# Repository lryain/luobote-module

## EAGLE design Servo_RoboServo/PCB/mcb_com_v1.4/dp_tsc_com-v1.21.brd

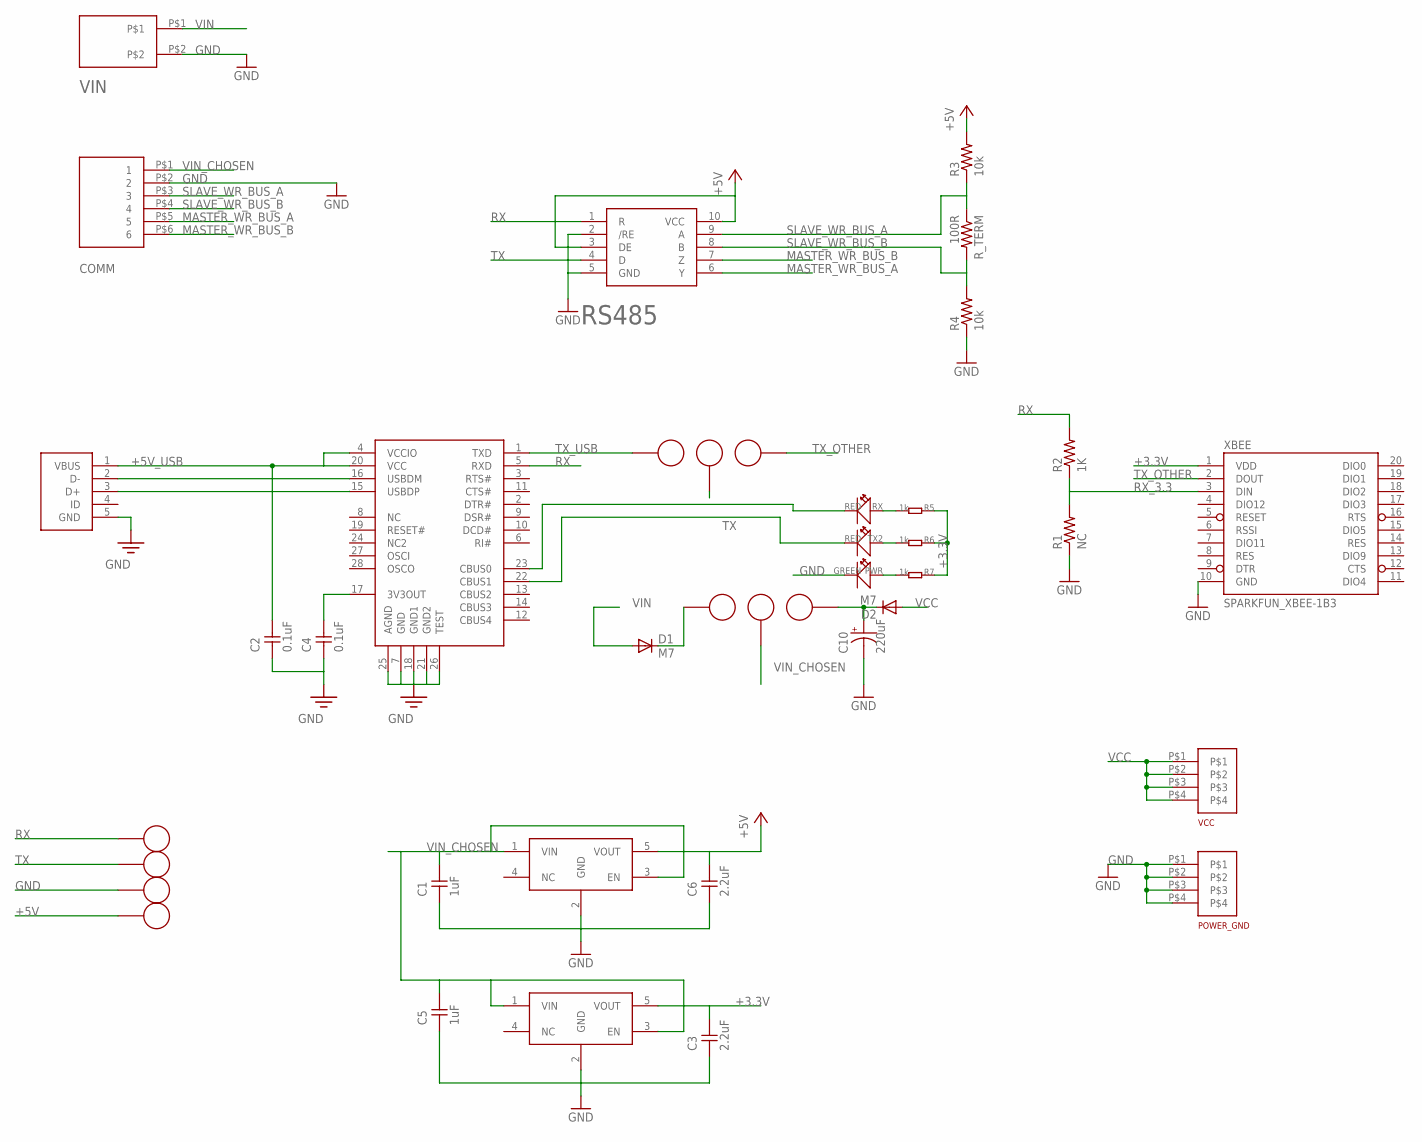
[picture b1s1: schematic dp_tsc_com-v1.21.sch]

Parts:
3.3V_REG, 5V_REG: MIC5235; SOT-23-5
5V1, 5V_USB1, 5V_VREG1: CONNECTOR_TV
+5V: CONNECTOR_TV
C1, C5: 1uF; 0805@1
C2, C4: 0.1uF; 0805@1
C3, C6: 2.2uF; 0805@1
C10: 220uF; HAO
COMM: 6PIN-RIBBONCABLE-BOARDHEADER; 6PIN-HEADER-DUALROW
D1, D2: M7; DO214BA
FT323R: FT232R; SSOP-28
GND: CONNECTOR_TV
POWER_GND: SCREW_TERMINAL_7700K; SCREW_TERM_7700K
PWR: GREEN; LED0603_S
R1: NC; 0603
R2: 1K; 0603
R3, R4: 10k; 0603
R5, R6, R7: 1k; 0603_S
RS485: RS485-SN65HVD3086EDGSR; MSOP-10
RX: RED; LED0603_S
RX1: CONNECTOR_TV
R_TERM: 100R; 0603
TX, TX1: CONNECTOR_TV
TX2: RED; LED0603_S
TX_FTDI: CONNECTOR_TV
TX_TTL: CONNECTOR_TV
USB: MINIUSB; UX60-MINI-USB
VCC: SCREW_TERMINAL_7700K; SCREW_TERM_7700K
VIN: 2PIN-3.81MM-TERMINAL-BLOCK; 2PIN-TERMINAL-BLOCK-SMALLER
XBEE: SPARKFUN_XBEE-1B3; SPARKFUN_XBEE-SMD

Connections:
+3.3V: 3.3V_REG.5 (VOUT), C3.2, R5.1, R6.1, R7.1, XBEE.1 (VDD)
+5V: 5V_REG.5 (VOUT), +5V.P$1, C6.2, R3.2, RS485.3 (DE), RS485.10 (VCC)
+5V_USB: C2.2, FT323R.4 (VCCIO), FT323R.20 (VCC), USB.1 (VBUS)
D+: FT323R.15 (USBDP), USB.3 (D+)
D-: FT323R.16 (USBDM), USB.2 (D-)
GND: 3.3V_REG.2 (GND), 5V_REG.2 (GND), C1.1, C2.1, C3.1, C4.1, C5.1, C6.1, C10.-, COMM.P$2 (2), FT323R.7 (GND), FT323R.18 (GND1), FT323R.21 (GND2), FT323R.25 (AGND), FT323R.26 (TEST), GND.P$1, POWER_GND.P$1, POWER_GND.P$2, POWER_GND.P$3, POWER_GND.P$4, PWR.2 (-), R1.1, R4.1, RS485.2 (/RE), RS485.5 (GND), USB.5 (GND), VIN.P$2, XBEE.10 (GND)
MASTER_WR_BUS_A: COMM.P$5 (5), RS485.6 (Y)
MASTER_WR_BUS_B: COMM.P$6 (6), RS485.7 (Z)
unnamed: 5V_USB1.P$1, C10.+, D2.C
unnamed: R6.2, TX2.1 (+)
unnamed: R5.2, RX.1 (+)
unnamed: C4.2, FT323R.17 (3V3OUT)
unnamed: PWR.1 (+), R7.2
unnamed: 5V_VREG1.P$1, D1.C
RX: FT323R.5 (RXD), R2.2, RS485.1 (R), RX1.P$1
RXING: FT323R.23 (CBUS0), RX.2 (-)
RX_3.3: R1.2, R2.1, XBEE.3 (DIN)
SLAVE_WR_BUS_A: COMM.P$3 (3), R3.1, RS485.9 (A), R_TERM.1
SLAVE_WR_BUS_B: COMM.P$4 (4), R4.2, RS485.8 (B), R_TERM.2
TX: RS485.4 (D), TX.P$1, TX1.P$1
TXING: FT323R.22 (CBUS1), TX2.2 (-)
TX_OTHER: TX_TTL.P$1, XBEE.2 (DOUT)
TX_USB: FT323R.1 (TXD), TX_FTDI.P$1
VCC: D2.A, VCC.P$1, VCC.P$2, VCC.P$3, VCC.P$4
VIN: D1.A, VIN.P$1
VIN_CHOSEN: 3.3V_REG.1 (VIN), 3.3V_REG.3 (EN), 5V1.P$1, 5V_REG.1 (VIN), 5V_REG.3 (EN), C1.2, C5.2, COMM.P$1 (1)

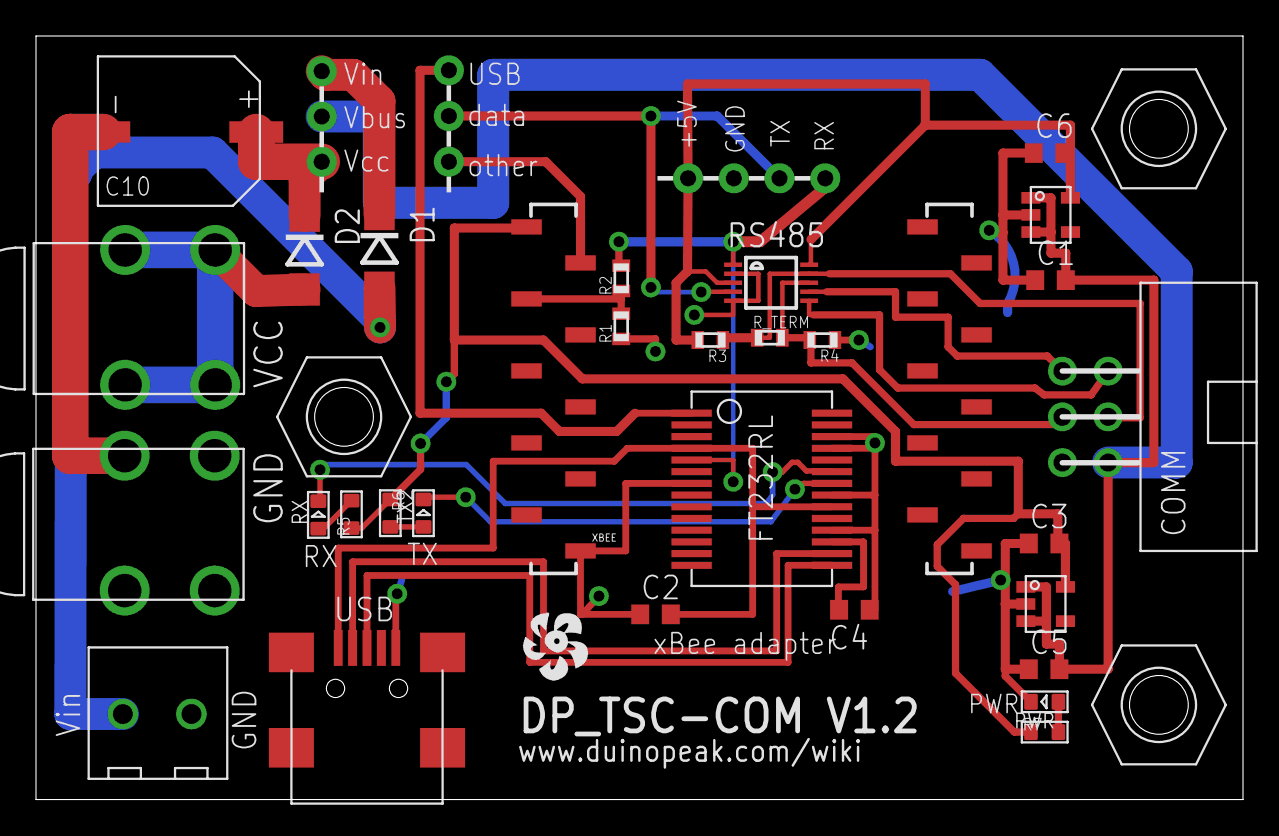
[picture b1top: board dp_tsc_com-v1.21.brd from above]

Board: 2 copper layers, 67.1 x 42.4 mm, 45 parts (0 on the bottom side), 26 nets.

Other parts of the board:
U$1: DUINOFUN-LOGO-PCB-0.5
U$2, U$3, U$14: 4-40_NUT_DRILL
U$5: DUINOFUN-BIG-LOGO-3.0

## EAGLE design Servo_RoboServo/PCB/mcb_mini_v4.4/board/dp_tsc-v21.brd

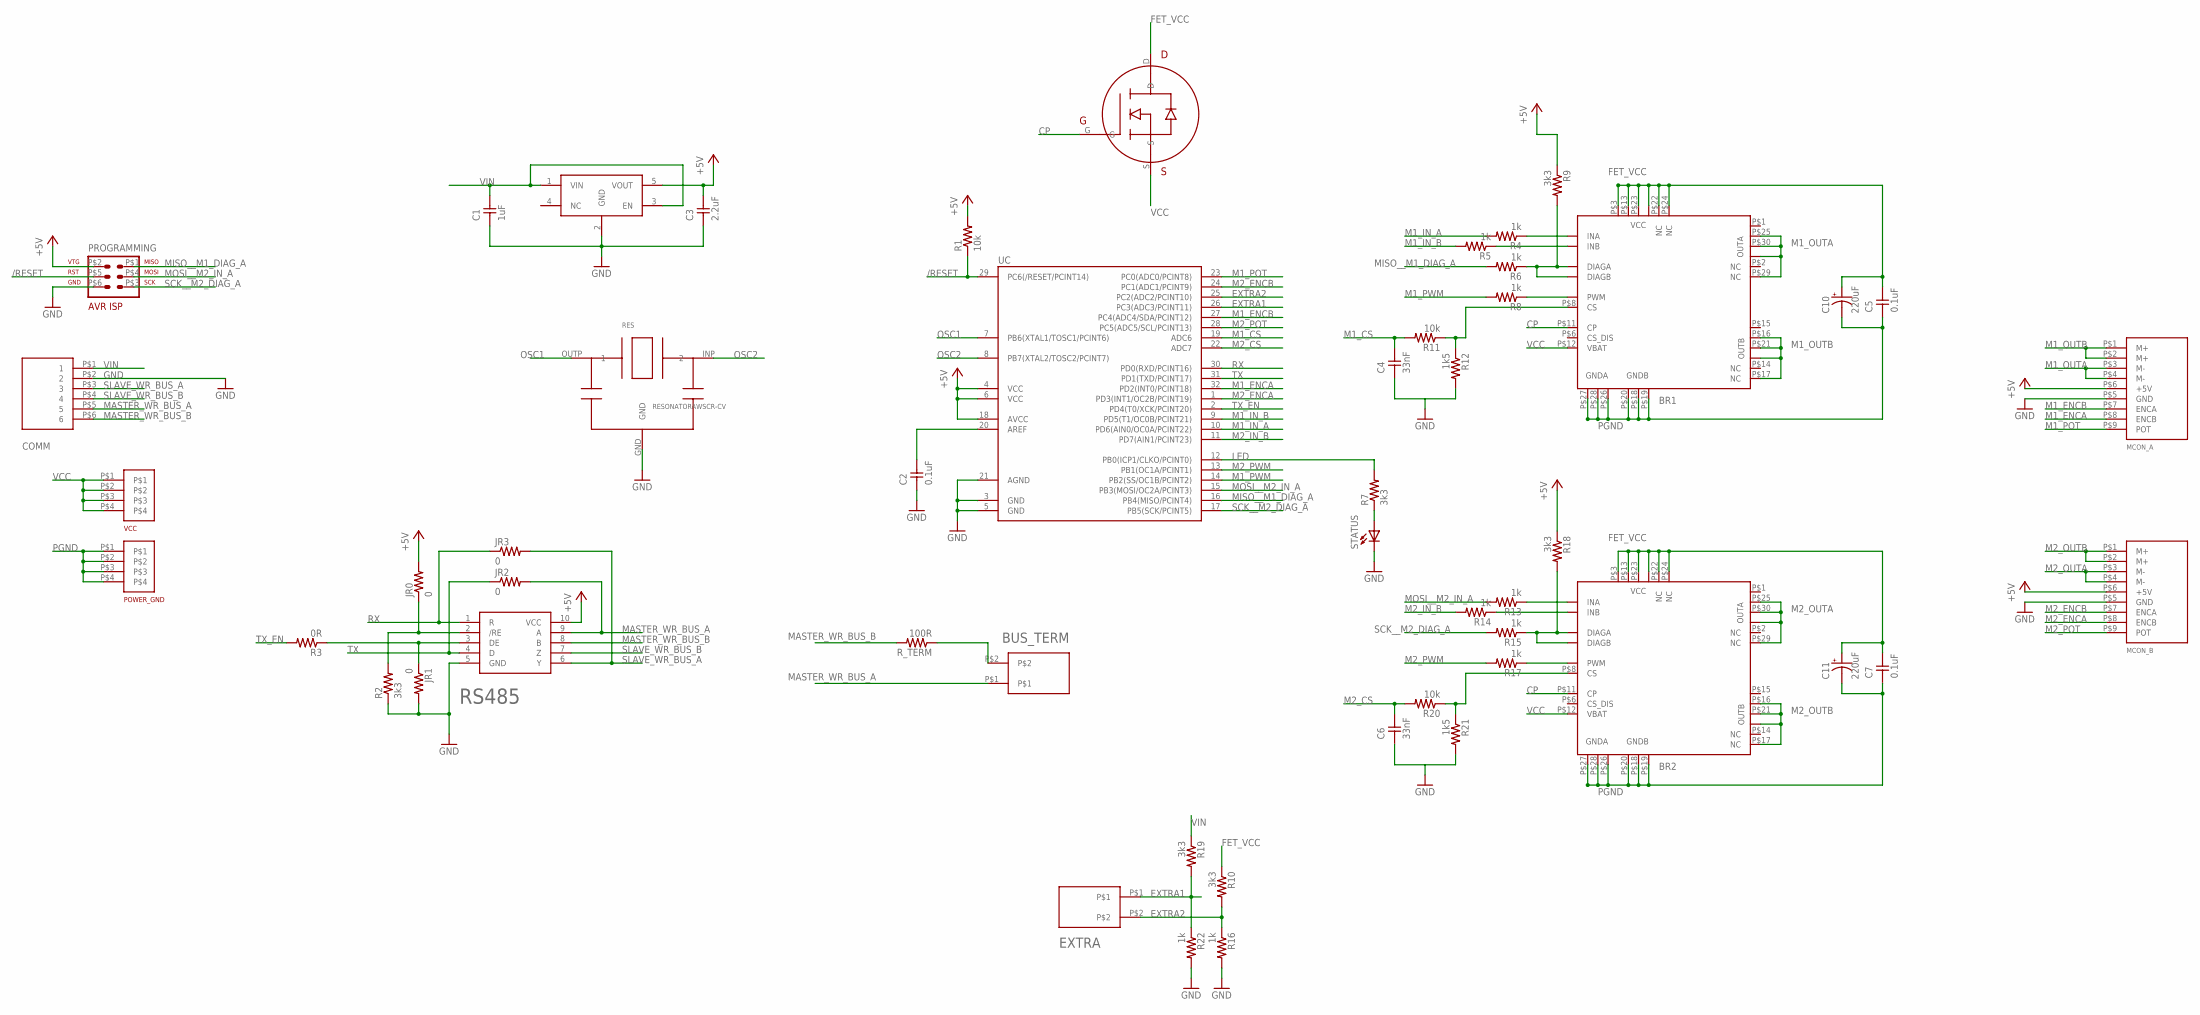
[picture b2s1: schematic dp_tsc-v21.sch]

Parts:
BR1, BR2: VNH5019A-E; MULTIPOWERSO-30-SIGGI
BUS_TERM: 2PIN-100MILL; 2-PIN-100MIL
C1: 1uF; 0603
C2, C5, C7: 0.1uF; 0603
C3: 2.2uF; 0603
C4, C6: 33nF; 0603
C10, C11: 220uF; HAO
COMM: 6PIN-RIBBONCABLE-BOARDHEADER; 6PIN-HEADER-DUALROW
EXTRA: 2PIN-100MILL; 2-PIN-100MIL
FET: MOSFET-N-FDD8896; TO-252
JR0, JR1, JR2, JR3: 0; 0603
MCON_A: 9-PIN-MOTOR_CONNECTOR; 9-PIN-2.54MM-TERMINAL-BLOCK
MCON_B: 9-PIN-MOTOR_CONNECTOR; 9-PIN-2.54MM-TERMINAL-BLOCK
POWER_GND: SCREW_TERMINAL_7700K; SCREW_TERM_7700K
PROGRAMMING: AVR-ISP-6SURFACE_MOUNT; SMD6
R1, R11, R20: 10k; 0603
R2, R7, R9, R10, R18, R19: 3k3; 0603
R3: 0R; 0603
R4, R5, R6, R8, R13, R14, R15, R16, R17, R22: 1k; 0603
R12, R21: 1k5; 0603
RES: RESONATORAWSCR-CV; AWSCR-CV
RS485: RS485-SN65HVD3086EDGSR; MSOP-10
R_TERM: 100R; 0603
STATUS: LED1206; CHIPLED_1206
UC: MEGA48/88/168-AU; TQFP32-08
VCC: SCREW_TERMINAL_7700K; SCREW_TERM_7700K
VREG: MIC5235; SOT-23-5

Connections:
+1.1V: C2.2, UC.20 (AREF)
+5V: C3.2, JR0.2, MCON_A.P$6 (+5V), MCON_B.P$6 (+5V), PROGRAMMING.P$2 (2), R1.2, R9.1, R18.1, RS485.10 (VCC), UC.4 (VCC), UC.6 (VCC), UC.18 (AVCC), VREG.5 (VOUT)
/RESET: PROGRAMMING.P$5 (5), R1.1, UC.29 (PC6(/RESET/PCINT14))
CP: BR1.P$11 (CP), BR2.P$11 (CP), FET.G
EXTRA1: EXTRA.P$1, R19.2, R22.1, UC.26 (PC3(ADC3/PCINT11))
EXTRA2: EXTRA.P$2, R10.2, R16.1, UC.25 (PC2(ADC2/PCINT10))
FET_VCC: BR1.P$3 (VCC), BR1.P$13 (VCC), BR1.P$22 (NC), BR1.P$23 (VCC), BR1.P$24 (NC), BR1.VCC_SLUG (VCC), BR2.P$3 (VCC), BR2.P$13 (VCC), BR2.P$22 (NC), BR2.P$23 (VCC), BR2.P$24 (NC), BR2.VCC_SLUG (VCC), C5.2, C7.2, C10.+, C11.+, FET.D, R10.1
GND: C1.1, C2.1, C3.1, C4.1, C6.1, COMM.P$2 (2), JR1.2, MCON_A.P$5 (GND), MCON_B.P$5 (GND), PROGRAMMING.P$6 (6), R2.1, R12.2, R16.2, R21.2, R22.2, RES.GND, RS485.5 (GND), STATUS.C, UC.3 (GND), UC.5 (GND), UC.21 (AGND), VREG.2 (GND)
LED: R7.2, UC.12 (PB0(ICP1/CLKO/PCINT0))
M1_CS: C4.2, R11.2, UC.19 (ADC6)
M1_ENCA: MCON_A.P$8 (ENCB), UC.32 (PD2(INT0/PCINT18))
M1_ENCB: MCON_A.P$7 (ENCA), UC.27 (PC4(ADC4/SDA/PCINT12))
M1_IN_A: R4.2, UC.10 (PD6(AIN0/OC0A/PCINT22))
M1_IN_B: R5.2, UC.9 (PD5(T1/OC0B/PCINT21))
M1_OUTA: BR1.OUTA_SLUG (OUTA), BR1.P$25 (OUTA), BR1.P$29 (NC), BR1.P$30 (OUTA), MCON_A.P$3 (M-), MCON_A.P$4 (M-)
M1_OUTB: BR1.OUTB_SLUG (OUTB), BR1.P$16 (OUTB), BR1.P$17 (NC), BR1.P$21 (OUTB), MCON_A.P$1 (M+), MCON_A.P$2 (M+)
M1_POT: MCON_A.P$9 (POT), UC.23 (PC0(ADC0/PCINT8))
M1_PWM: R8.2, UC.14 (PB2(SS/OC1B/PCINT2))
M2_CS: C6.2, R20.2, UC.22 (ADC7)
M2_ENCA: MCON_B.P$8 (ENCB), UC.1 (PD3(INT1/OC2B/PCINT19))
M2_ENCB: MCON_B.P$7 (ENCA), UC.24 (PC1(ADC1/PCINT9))
M2_IN_B: R14.2, UC.11 (PD7(AIN1/PCINT23))
M2_OUTA: BR2.OUTA_SLUG (OUTA), BR2.P$25 (OUTA), BR2.P$29 (NC), BR2.P$30 (OUTA), MCON_B.P$3 (M-), MCON_B.P$4 (M-)
M2_OUTB: BR2.OUTB_SLUG (OUTB), BR2.P$16 (OUTB), BR2.P$17 (NC), BR2.P$21 (OUTB), MCON_B.P$1 (M+), MCON_B.P$2 (M+)
M2_POT: MCON_B.P$9 (POT), UC.28 (PC5(ADC5/SCL/PCINT13))
M2_PWM: R17.2, UC.13 (PB1(OC1A/PCINT1))
MASTER_WR_BUS_A: BUS_TERM.P$1, COMM.P$5 (5), JR2.2, RS485.9 (A)
MASTER_WR_BUS_B: COMM.P$6 (6), RS485.8 (B), R_TERM.2
MISO__M1_DIAG_A: PROGRAMMING.P$1 (1), R6.2, UC.16 (PB4(MISO/PCINT4))
MOSI__M2_IN_A: PROGRAMMING.P$4 (4), R13.2, UC.15 (PB3(MOSI/OC2A/PCINT3))
unnamed: BR2.P$4 (INA), R13.1
unnamed: JR0.1, R2.2, RS485.2 (/RE)
unnamed: JR1.1, R3.1, RS485.3 (DE)
unnamed: BR1.P$8 (CS), R11.1, R12.1
unnamed: BR2.P$10 (INB), R14.1
unnamed: BR2.P$5 (DIAGA), BR2.P$9 (DIAGB), R15.1, R18.2
unnamed: BR2.P$7 (PWM), R17.1
unnamed: BR1.P$4 (INA), R4.1
unnamed: BR1.P$10 (INB), R5.1
unnamed: R7.1, STATUS.A
unnamed: BR1.P$5 (DIAGA), BR1.P$9 (DIAGB), R6.1, R9.2
unnamed: BR1.P$7 (PWM), R8.1
unnamed: BR2.P$8 (CS), R20.1, R21.1
unnamed: BUS_TERM.P$2, R_TERM.1
OSC1: RES.OUTP (1), UC.7 (PB6(XTAL1/TOSC1/PCINT6))
OSC2: RES.INP (2), UC.8 (PB7(XTAL2/TOSC2/PCINT7))
PGND: BR1.P$18 (GNDB), BR1.P$19 (GNDB), BR1.P$20 (GNDB), BR1.P$26 (GNDA), BR1.P$27 (GNDA), BR1.P$28 (GNDA), BR2.P$18 (GNDB), BR2.P$19 (GNDB), BR2.P$20 (GNDB), BR2.P$26 (GNDA), BR2.P$27 (GNDA), BR2.P$28 (GNDA), C5.1, C7.1, C10.-, C11.-, POWER_GND.P$1, POWER_GND.P$2, POWER_GND.P$3, POWER_GND.P$4
RX: JR3.1, RS485.1 (R), UC.30 (PD0(RXD/PCINT16))
SCK__M2_DIAG_A: PROGRAMMING.P$3 (3), R15.2, UC.17 (PB5(SCK/PCINT5))
SLAVE_WR_BUS_A: COMM.P$3 (3), JR3.2, RS485.6 (Y)
SLAVE_WR_BUS_B: COMM.P$4 (4), RS485.7 (Z)
TX: JR2.1, RS485.4 (D), UC.31 (PD1(TXD/PCINT17))
TX_EN: R3.2, UC.2 (PD4(T0/XCK/PCINT20))
VCC: BR1.P$12 (VBAT), BR2.P$12 (VBAT), FET.S, VCC.P$1, VCC.P$2, VCC.P$3, VCC.P$4
VIN: C1.2, COMM.P$1 (1), R19.1, VREG.1 (VIN), VREG.3 (EN)

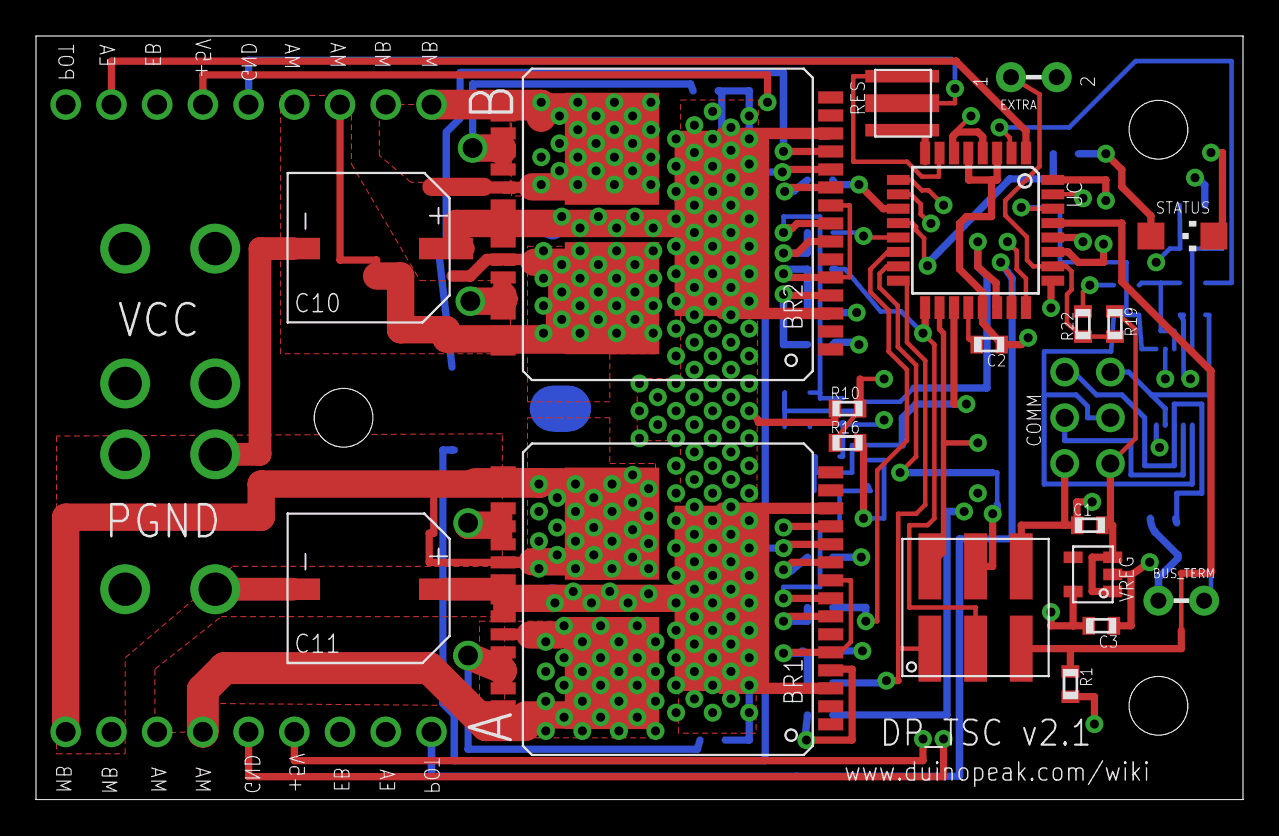
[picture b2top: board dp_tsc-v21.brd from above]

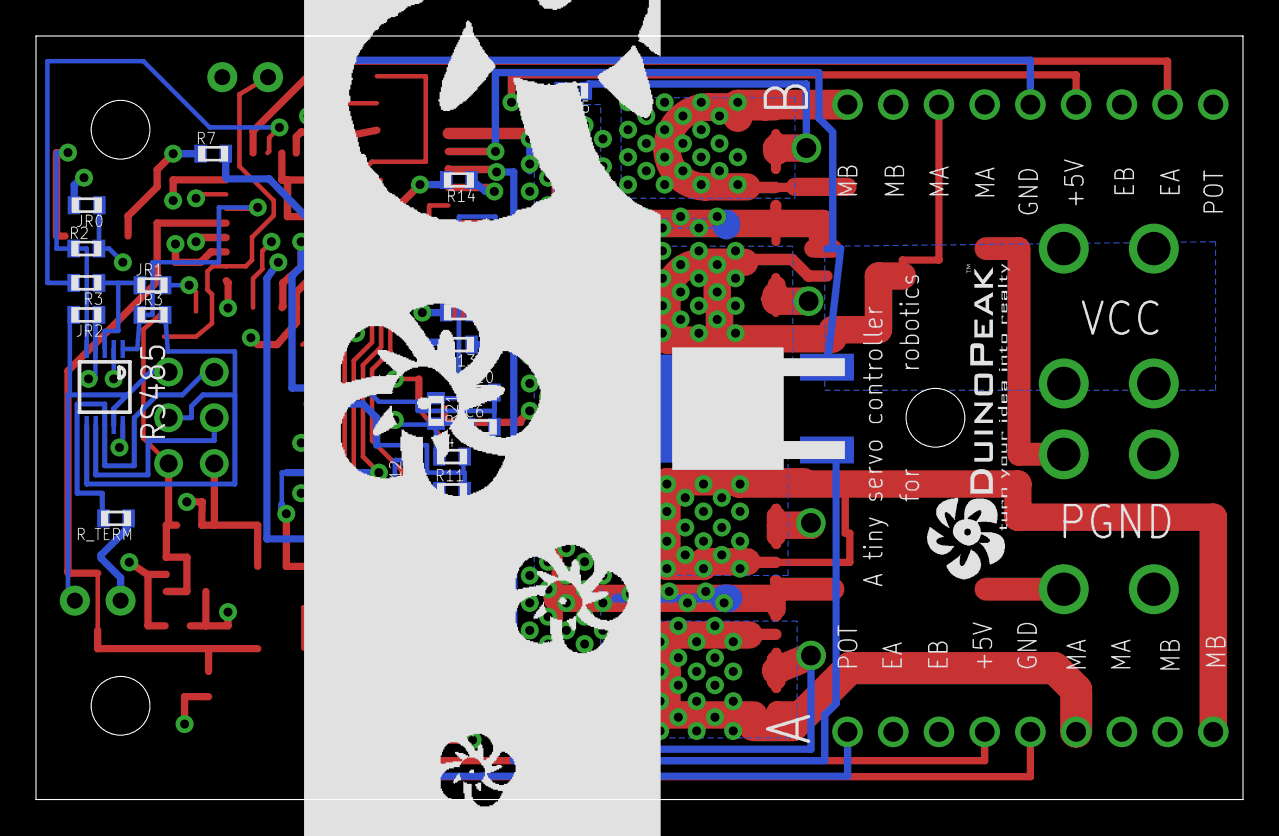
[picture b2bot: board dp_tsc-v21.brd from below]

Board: 2 copper layers, 67.1 x 42.4 mm, 57 parts (29 on the bottom side), 55 nets.

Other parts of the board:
U$1: DUINOFUN-BIG-LOGO-2.6
U$2: DUINOPEAK-LOGO-0.6
U$3, U$10, U$14: 4-40_NUT_DRILL

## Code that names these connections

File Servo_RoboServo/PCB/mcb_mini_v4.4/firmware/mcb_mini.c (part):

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			CLEARBIT(EXTRA1_DDR, EXTRA1);
			SETBIT(EXTRA1_PORT, EXTRA1);
			SETBIT(PCMSK1, EXTRA1);
			motor[channel].extra_switch = BITVAL(EXTRA1_PIN, EXTRA1);
			// Send the current level of the switch
			SETBIT( RX_FLAGS, FLAG_SHOULD_SEND_EXTRA_VAL_A );
		}
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			CLEARBIT(EXTRA2_DDR, EXTRA2);
			SETBIT(EXTRA2_PORT, EXTRA2);
			SETBIT(PCMSK1, EXTRA2);
			motor[channel].extra_switch = BITVAL(EXTRA2_PIN, EXTRA2);
			// Send the current level of the switch
			SETBIT( RX_FLAGS, FLAG_SHOULD_SEND_EXTRA_VAL_B );
		}
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	SETBIT(EIMSK, INT1);

	// Sets the bridge into High z state
	M1_PWM = 0;
	M2_PWM = 0;

	// Init uart
	SETBIT(UCSR0B, RXCIE0);
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// This gets called whenever the EXTRA pins are setup as switches and change value
ISR(PCINT1_vect){
	// If it was EXTRA1
	if( BITVAL(EXTRA1_PIN, EXTRA1) != motor[0].extra_switch ){
		motor[0].extra_switch = BITVAL(EXTRA1_PIN, EXTRA1);
		SETBIT( RX_FLAGS, FLAG_SHOULD_SEND_EXTRA_VAL_A );
	}
	if( BITVAL(EXTRA2_PIN, EXTRA2) != motor[1].extra_switch ){
		motor[1].extra_switch = BITVAL(EXTRA2_PIN, EXTRA2);
		SETBIT( RX_FLAGS, FLAG_SHOULD_SEND_EXTRA_VAL_B );
	}
}
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//		addMessage1(CMD_ERROR, 0, ERROR_FAULT);

		// Reset the bridge
		M1_PWM = 0;
		M1_STOP_GND;
		_delay_us(100);
		M1_STOP_VCC;
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//		addMessage1(CMD_ERROR, 1, ERROR_FAULT);

		// Reset the bridge
		M2_PWM = 0;
		M2_STOP_GND;
		_delay_us(100);
		M2_STOP_VCC;
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
// M1_ENCA changed state
ISR(INT0_vect){
	if( BITSET(M1_ENCB_PIN, M1_ENCB) ){
		if( BITSET(M1_ENCA_PIN, M1_ENCA) ) 	motor[0].encoder_increment--;
		else								motor[0].encoder_increment++;
	}
	else{
		if( BITSET(M1_ENCA_PIN, M1_ENCA) ) 	motor[0].encoder_increment++;
		else								motor[0].encoder_increment--;
	}
}

// M2_ENCA changed state
ISR(INT1_vect){
	if( BITSET(M2_ENCB_PIN, M2_ENCB) ){
		if( BITSET(M2_ENCA_PIN, M2_ENCA) ) 	motor[1].encoder_increment--;
		else								motor[1].encoder_increment++;
	}
	else{
		if( BITSET(M2_ENCA_PIN, M2_ENCA) ) 	motor[1].encoder_increment++;
		else								motor[1].encoder_increment--;
	}
}
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
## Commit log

2016-12-22 Cam_AVRCam
2016-12-22 Servo_RoboServo

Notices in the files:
Servo_RoboServo/PCB/mcb_mini_v4.4/firmware/mcb_mini.c:
MCBMini firmware is free software: you can redistribute it and/or modify
it under the terms of the GNU General Public License as published by
the Free Software Foundation, version 2 of the License
